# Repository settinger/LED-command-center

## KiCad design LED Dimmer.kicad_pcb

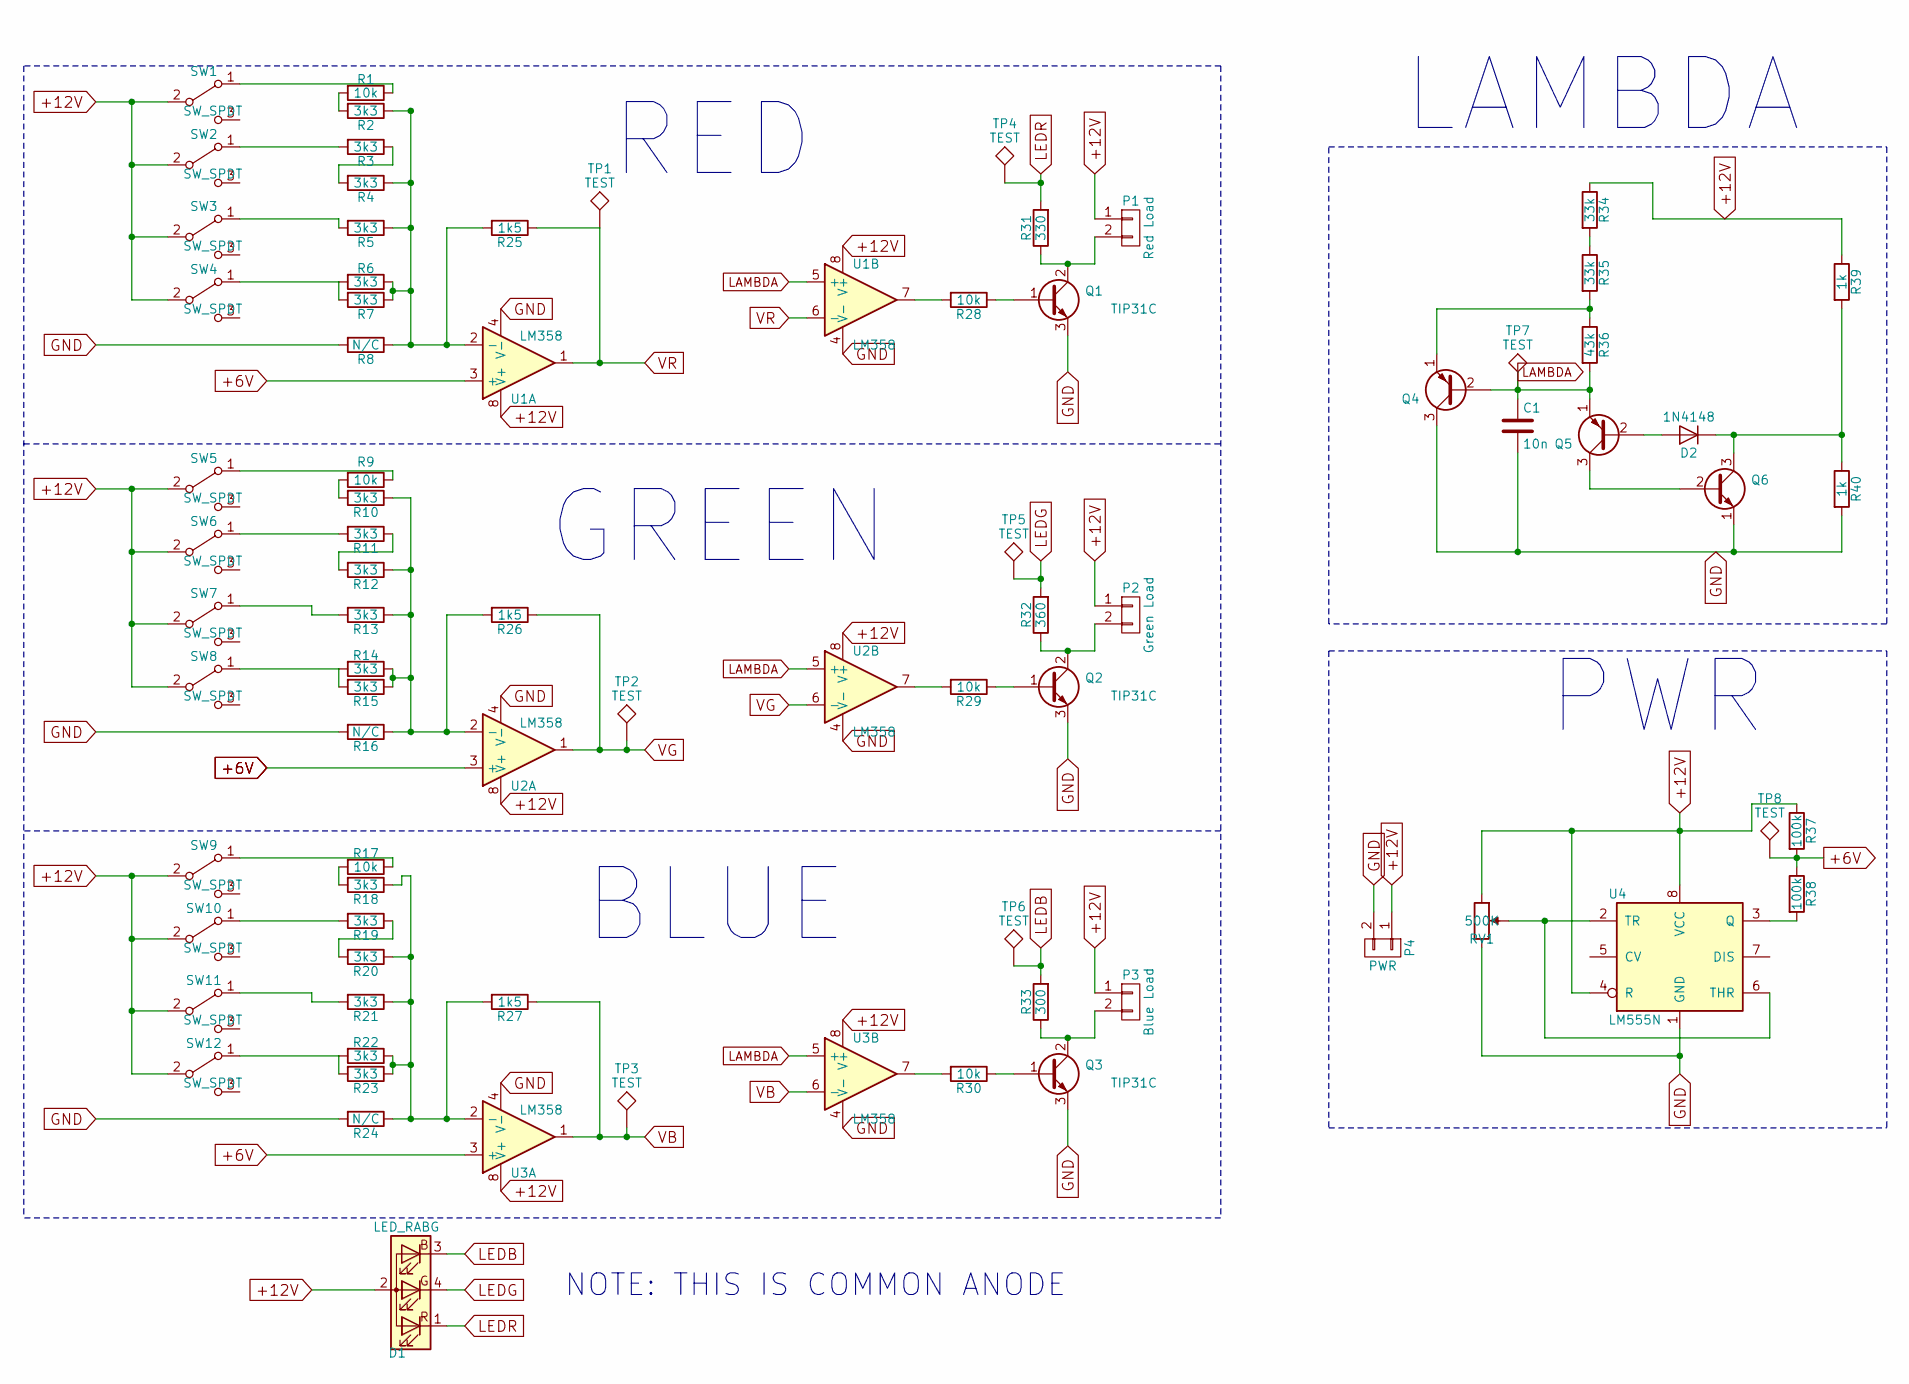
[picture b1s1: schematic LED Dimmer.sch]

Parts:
C1: 10n; C_Disc
D1: LED_RABG; LED_D5.0mm-4
D2: 1N4148; D_axial
P1: Red Load; 2.1ID_5.5OD_SIDE_MOUNT_JACK
P2: Green Load; 2.1ID_5.5OD_SIDE_MOUNT_JACK
P3: Blue Load; 2.1ID_5.5OD_SIDE_MOUNT_JACK
P4: PWR; 2.1ID_5.5OD_SIDE_MOUNT_JACK
Q1, Q2, Q3: TIP31C; TO-220_Vertical
Q4, Q5: Q_PNP_EBC; TO-92_Molded_Wide
Q6: Q_NPN_EBC; TO-92_Molded_Wide
R1, R9, R17, R28, R29, R30: 10k; R_Axial
R2, R3, R4, R5, R6, R7, R10, R11, R12, R13, R14, R15, R18, R19, R20, R21, R22, R23: 3k3; R_Axial
R8, R16, R24: N/C; R_Axial
R25, R26, R27: 1k5; R_Axial
R31: 330; R_Axial
R32: 360; R_Axial
R33: 300; R_Axial
R34, R35: 33k; R_Axial
R36: 43k; R_Axial
R37, R38: 100k; R_Axial
R39, R40: 1k; R_Axial
RV1: 500K; POT_UM_296RE
SW1, SW2, SW3, SW4, SW5, SW6, SW7, SW8, SW9, SW10, SW11, SW12: SW_SPDT; SW_SPDT_PCBPM
TP1, TP2, TP3, TP4, TP5, TP6, TP7, TP8: TEST; test_pt_alt
U1, U2, U3: LM358; DIP8_dualopamp
U4: LM555N; DIP8

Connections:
+6V: R37.2, R38.1, TP8.1, U1.3 (+), U2.3 (+), U3.3 (+)
+12V: D1.2 (A), P1.1, P2.1, P3.1, P4.1, R34.1, R37.1, R39.1, RV1.1, SW1.2 (B), SW2.2 (B), SW3.2 (B), SW4.2 (B), SW5.2 (B), SW6.2 (B), SW7.2 (B), SW8.2 (B), SW9.2 (B), SW10.2 (B), SW11.2 (B), SW12.2 (B), U1.8 (V+), U2.8 (V+), U3.8 (V+), U4.4 (R), U4.8 (VCC)
GND: C1.2, P4.2, Q1.3 (E), Q2.3 (E), Q3.3 (E), Q4.3 (C), Q6.1 (E), R8.2, R16.2, R24.2, R40.2, RV1.3, U1.4 (V-), U2.4 (V-), U3.4 (V-), U4.1 (GND)
LAMBDA: C1.1, Q4.2 (B), Q5.1 (E), R36.2, TP7.1, U1.5 (+), U2.5 (+), U3.5 (+)
LEDB: D1.3 (BK), R33.2, TP6.1
LEDG: D1.4 (GK), R32.2, TP5.1
LEDR: D1.1 (RK), R31.2, TP4.1
unnamed: D2.1 (K), Q6.3 (C), R39.2, R40.1
unnamed: D2.2 (A), Q5.2 (B)
unnamed: P1.2, Q1.2 (C), R31.1
unnamed: P2.2, Q2.2 (C), R32.1
unnamed: P3.2, Q3.2 (C), R33.1
unnamed: Q1.1 (B), R28.1
unnamed: Q2.1 (B), R29.1
unnamed: Q3.1 (B), R30.1
unnamed: Q4.1 (E), R35.2, R36.1
unnamed: Q5.3 (C), Q6.2 (B)
unnamed: R1.1, SW1.1 (A)
unnamed: R1.2, R2.2
unnamed: R2.1, R4.1, R5.1, R6.1, R7.1, R8.1, R25.2, U1.2 (-)
unnamed: R3.1, R4.2
unnamed: R3.2, SW2.1 (A)
unnamed: R5.2, SW3.1 (A)
unnamed: R6.2, R7.2, SW4.1 (A)
unnamed: R9.1, SW5.1 (A)
unnamed: R10.1, R12.1, R13.1, R14.1, R15.1, R16.1, R26.2, U2.2 (-)
unnamed: R9.2, R10.2
unnamed: R11.1, R12.2
unnamed: R11.2, SW6.1 (A)
unnamed: R13.2, SW7.1 (A)
unnamed: R14.2, R15.2, SW8.1 (A)
unnamed: R17.1, SW9.1 (A)
unnamed: R17.2, R18.2
unnamed: R18.1, R20.1, R21.1, R22.1, R23.1, R24.1, R27.2, U3.2 (-)
unnamed: R19.1, R20.2
unnamed: R19.2, SW10.1 (A)
unnamed: R21.2, SW11.1 (A)
unnamed: R22.2, R23.2, SW12.1 (A)
unnamed: R28.2, U1.7
unnamed: R29.2, U2.7
unnamed: R30.2, U3.7
unnamed: R34.2, R35.1
unnamed: R38.2, U4.3 (Q)
unnamed: RV1.2, U4.2 (TR), U4.6 (THR)
VB: R27.1, TP3.1, U3.1, U3.6 (-)
VG: R26.1, TP2.1, U2.1, U2.6 (-)
VR: R25.1, TP1.1, U1.1, U1.6 (-)

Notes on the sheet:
PWR
LAMBDA
NOTE: THIS IS COMMON ANODE
RED
GREEN
BLUE

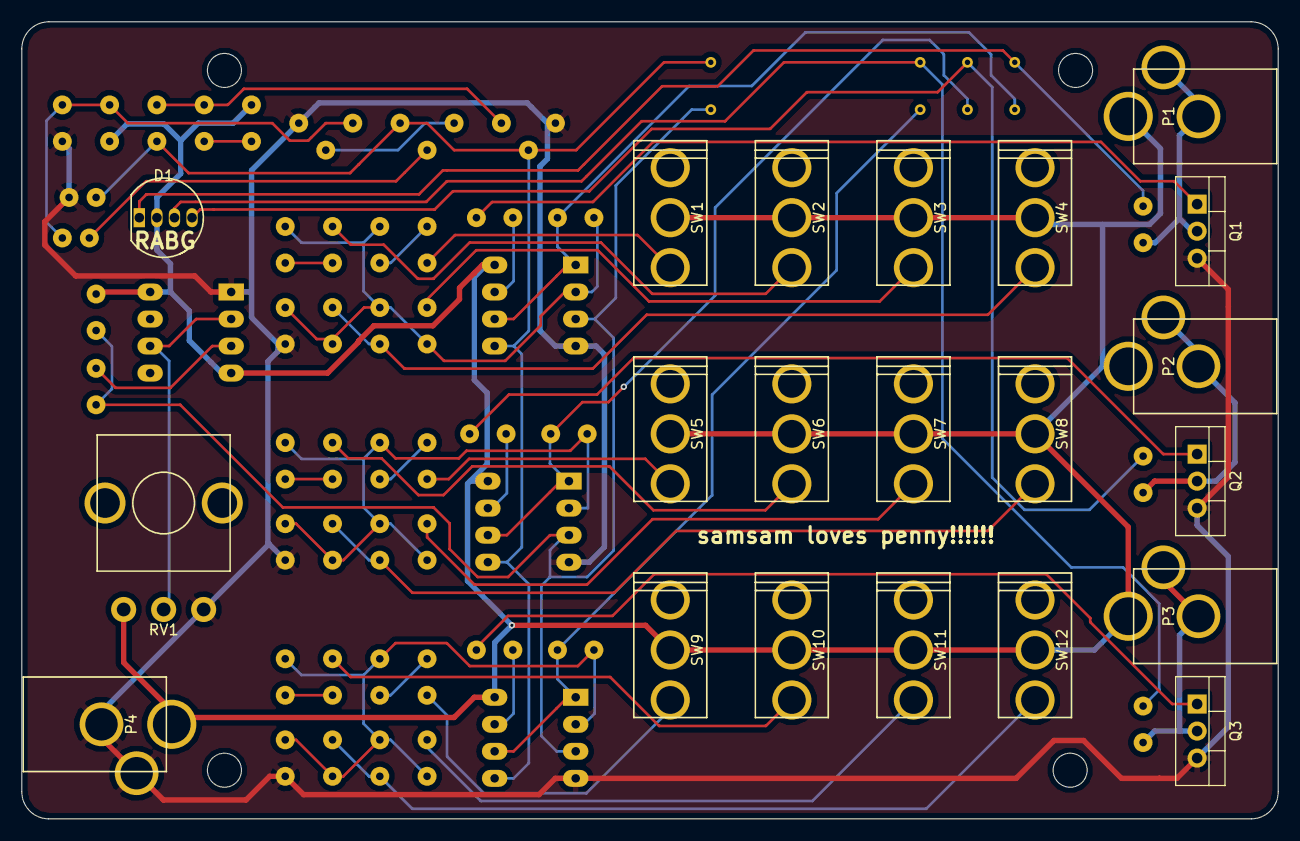
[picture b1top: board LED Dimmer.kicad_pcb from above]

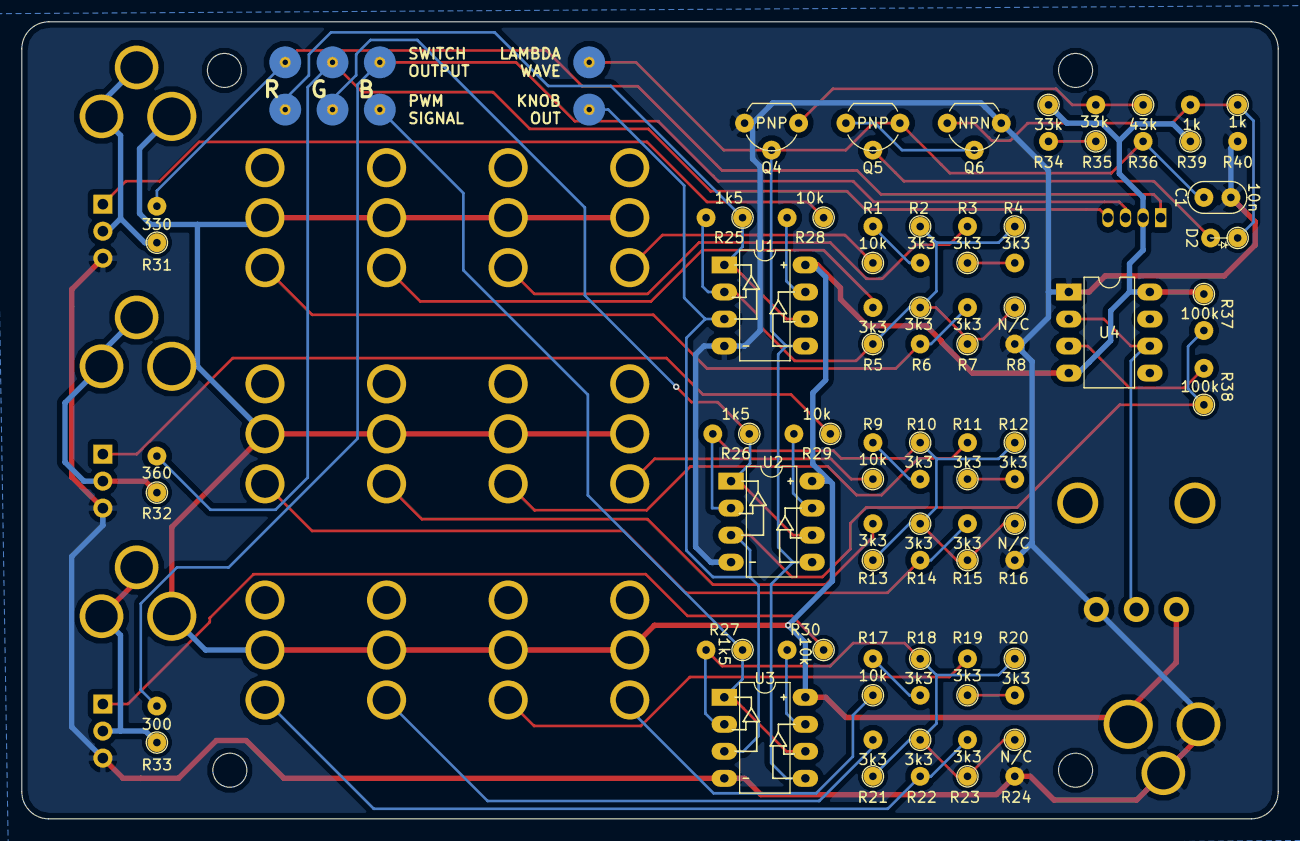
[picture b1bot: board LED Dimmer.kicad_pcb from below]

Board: 2 copper layers, 118.1 x 74.9 mm, 78 parts (57 on the bottom side), 47 nets.

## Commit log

2017-06-20 Added footprints
2017-06-20 Components placed, edge cuts marked, ready for routing
2017-06-20 Routed
2017-06-20 Nudged RGB LED to line up with knob; added front panel (without silks)
2017-06-20 prepping for front panel graphics
2017-06-21 Renamed library for compatibility with 3D viewer
2017-06-21 Rerouted around TO-92 footprints (in the last commit I grew the pads on TO-92 footprint but forgot to mention it)
2017-06-21 Updated 3d model (resized resistors)
2017-06-21 Added plug in WRL format
2017-06-21 Added a switch and a potentiometer (the wrong potentiometer) to WRLs
2017-06-23 Added mounting holes for M3 screws and re-routed accordingly
2017-06-23 Copper pour, maybe
2017-06-23 New gerbs
2017-06-23 Mounting holes resized to 3.2mm, added to front panel as well
2017-06-23 Rounded edges
2017-06-23 Front panel outline done, ready for graphics
2017-06-29 Added RED/GREEN/BLUE text to silkscreen, changed load resistor values to be a bit more conservative
2017-07-03 Finished front panel, I think
